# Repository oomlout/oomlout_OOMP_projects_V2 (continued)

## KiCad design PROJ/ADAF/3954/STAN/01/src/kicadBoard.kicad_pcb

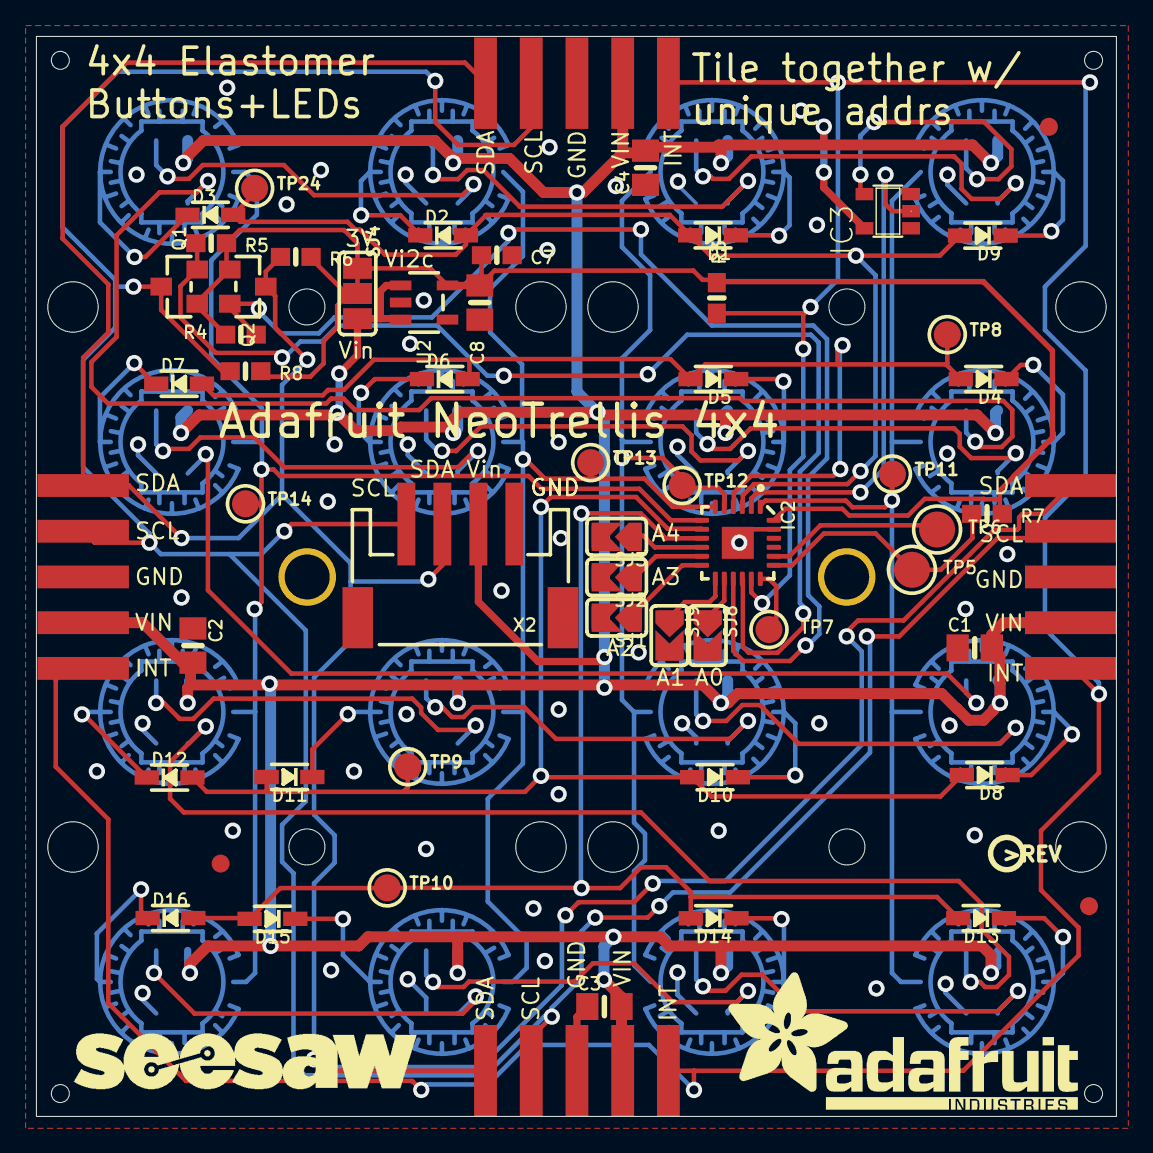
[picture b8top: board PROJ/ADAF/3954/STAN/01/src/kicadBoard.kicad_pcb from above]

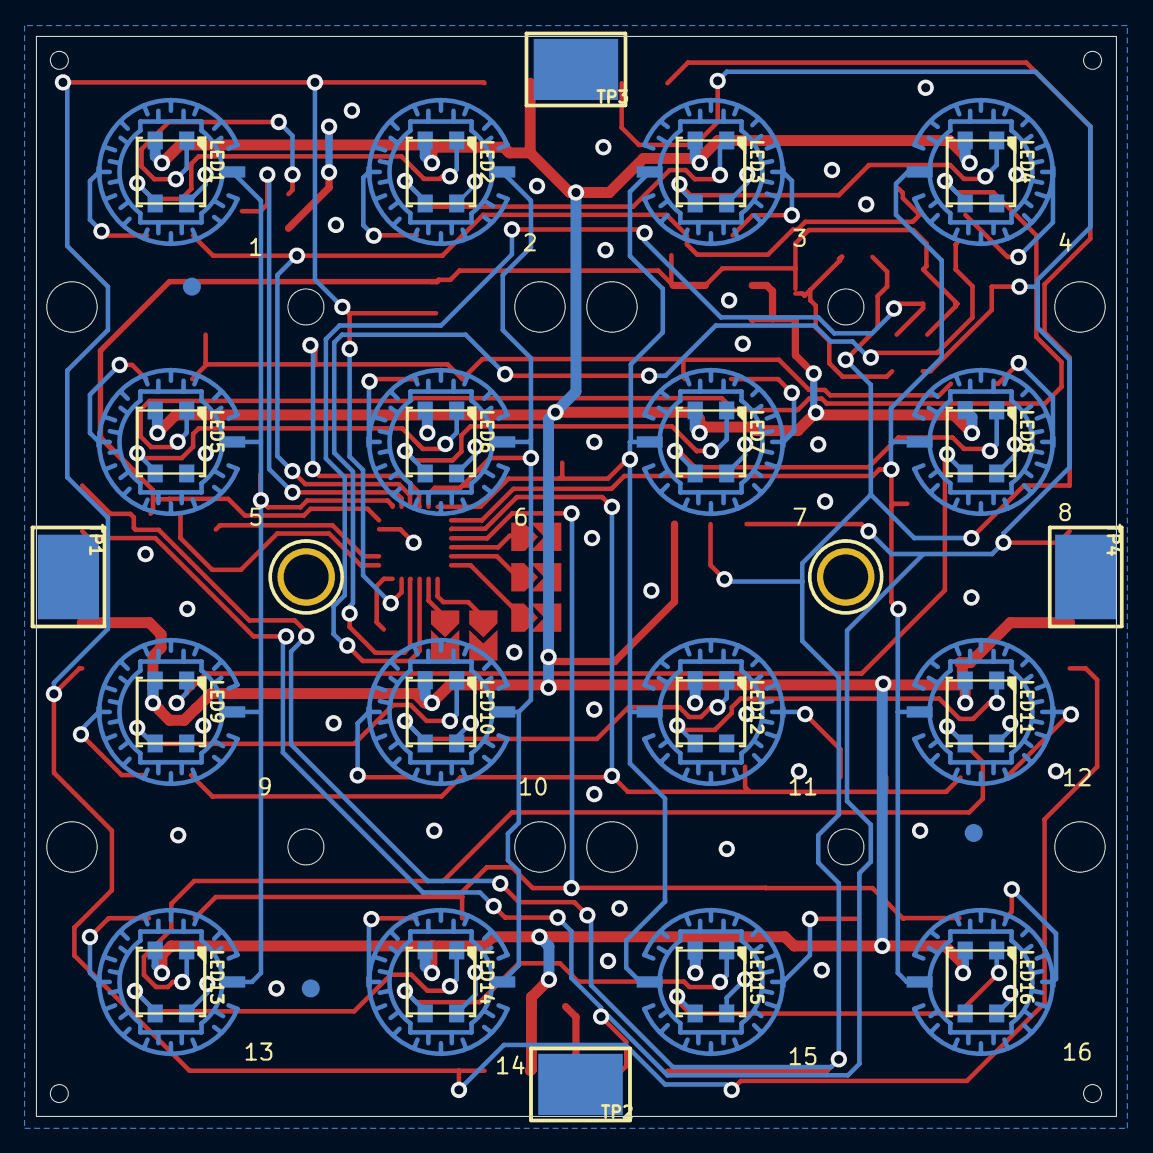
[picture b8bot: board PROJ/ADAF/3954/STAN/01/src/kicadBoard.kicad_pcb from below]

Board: 2 copper layers, 60.0 x 60.0 mm, 118 parts (41 on the bottom side), 58 nets.

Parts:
@HOLE0, @HOLE1, @HOLE2, @HOLE3, @HOLE4, @HOLE5, @HOLE6, @HOLE7, @HOLE8, @HOLE9, @HOLE10, @HOLE11, @HOLE12, @HOLE13, @HOLE14, @HOLE15: (no value)
C1, C2, C3, C4: 10u; 0805-NO
C7: 1uF; 0603-NO
C8: 10µF; 0805-NO
D1, D2, D3, D4, D5, D6, D7, D8, D9, D10, D11, D12, D13, D14, D15, D16: 1N4148; SOD-323
FID1, FID2, FID3, FID4, FID5, FID6: FIDUCIAL_1MM
IC2: ATSAMD09D14A-MU; QFN24_4MM
IC3: 74AHCT1G125DBV; SOT23-5
JP1, JP2, JP3, JP4: 5P_EDGECONNECT
LED1, LED2, LED3, LED4, LED5, LED6, LED7, LED8, LED9, LED10, LED11, LED12, LED13, LED14, LED15, LED16: WS2812B3535; LED3535
Q1, Q2: BSS138; SOT23-WIDE
R3: 10k; 0603-NO
R4, R5, R6, R7, R8: 10K; 0603-NO
SJ1, SJ2, SJ3, SJ8, SJ9: SOLDERJUMPER_ARROW_NOPASTE
SJ4: SOLDERJUMPER_2WAY_OPEN_NOPASTE
TP1, TP2, TP3, TP4: TESTPOINT_SMT
TP5, TP6: TESTPOINT_ROUND_2MM
TP7, TP8, TP9, TP10, TP11, TP12, TP13, TP14, TP24: TESTPOINT_ROUND_1.5MM
U2: AP2112-3.3; SOT23-5
U$1, U$2: MOUNTINGHOLE2.5; MOUNTINGHOLE_2.5_PLATED
U$3: ADAFRUIT_TEXT_20MM
U$4, U$5, U$6, U$7, U$8, U$9, U$10, U$11, U$12, U$23, U$24, U$25, U$26, U$27, U$28, U$29: ELAST_10X10; ELAST_PAD_SQUARE_10MM_4X4WIDE
U$14: SEESAW_LOGO
U$19: PCBFEAT-REV-040
X2: STEMMA_I2C_RASMT; JSTPH4

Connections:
3.3V: C7.1, C8.1, IC2.24, Q1.1, Q2.1, R3.2, R4.2, R5.2, R7.2, SJ4.1, U2.5
ADDR0: IC2.14, SJ8.1
ADDR1: IC2.13, SJ9.1
ADDR2: IC2.12, SJ1.1
ADDR3: IC2.11, SJ2.1
ADDR4: IC2.10, SJ3.1
COL0: IC2.1, TP11.P$1, U$4.P$1, U$8.P$1, U$12.P$1, U$26.P$1
COL1: IC2.5, TP12.P$1, U$5.P$1, U$9.P$1, U$23.P$1, U$27.P$1
COL2: IC2.6, TP13.P$1, U$6.P$1, U$10.P$1, U$25.P$1, U$28.P$1
COL3: IC2.7, TP14.P$1, U$7.P$1, U$11.P$1, U$24.P$1, U$29.P$1
GND: C1.1, C2.1, C3.1, C4.1, C7.2, C8.2, IC2.23, IC2.THERM, IC3.1, IC3.3, JP1.3, JP2.3, JP3.3, JP4.3, LED1.4, LED2.4, LED3.4, LED4.4, LED5.4, LED6.4, LED7.4, LED8.4, LED9.4, LED10.4, LED11.4, LED12.4, LED13.4, LED14.4, LED15.4, LED16.4, SJ1.2, SJ2.2, SJ3.2, SJ8.2, SJ9.2, U2.2, X2.1
INT: IC2.17, JP1.1, JP2.1, JP3.1, JP4.1, R3.1
LED_3V: IC2.2, IC3.2
LED_IN: IC3.4, LED1.1
unnamed: R6.2, R8.2, SJ4.2
unnamed: D9.C, U$4.P$2
unnamed: D1.C, U$5.P$2
unnamed: D2.C, U$6.P$2
unnamed: D3.C, U$7.P$2
unnamed: D4.C, U$8.P$2
unnamed: D5.C, U$9.P$2
unnamed: LED1.3, LED2.1
unnamed: LED2.3, LED3.1
unnamed: LED3.3, LED4.1
unnamed: LED4.3, LED5.1
unnamed: D6.C, U$10.P$2
unnamed: LED5.3, LED6.1
unnamed: LED6.3, LED7.1
unnamed: D7.C, U$11.P$2
unnamed: LED7.3, LED8.1
unnamed: D8.C, U$12.P$2
unnamed: LED8.3, LED9.1
unnamed: D10.C, U$23.P$2
unnamed: D11.C, U$25.P$2
unnamed: D12.C, U$24.P$2
unnamed: D13.C, U$26.P$2
unnamed: D14.C, U$27.P$2
unnamed: D15.C, U$28.P$2
unnamed: D16.C, U$29.P$2
unnamed: LED9.3, LED10.1
unnamed: LED10.3, LED12.1
unnamed: LED11.1, LED12.3
unnamed: LED11.3, LED13.1
unnamed: LED13.3, LED14.1
unnamed: LED14.3, LED15.1
unnamed: LED15.3, LED16.1
ROW0: D1.A, D2.A, D3.A, D9.A, IC2.3, TP24.P$1
ROW1: D4.A, D5.A, D6.A, D7.A, IC2.4, TP8.P$1
ROW2: D8.A, D10.A, D11.A, D12.A, IC2.8, TP9.P$1
ROW3: D13.A, D14.A, D15.A, D16.A, IC2.9, TP10.P$1
SCL: JP1.4, JP2.4, JP3.4, JP4.4, Q1.3, R8.1, X2.4
SCL_3V: IC2.16, Q1.2, R5.1
SDA: JP1.5, JP2.5, JP3.5, JP4.5, Q2.3, R6.1, X2.3
SDA_3V: IC2.15, Q2.2, R4.1
SWCLK: IC2.19, R7.1, TP5.P$1
SWDIO: IC2.20, TP6.P$1
VIN: C1.2, C2.2, C3.2, C4.2, IC3.5, JP1.2, JP2.2, JP3.2, JP4.2, LED1.2, LED2.2, LED3.2, LED4.2, LED5.2, LED6.2, LED7.2, LED8.2, LED9.2, LED10.2, LED11.2, LED12.2, LED13.2, LED14.2, LED15.2, LED16.2, SJ4.3, U2.1, U2.3, X2.2
~RESET: IC2.18, TP7.P$1
